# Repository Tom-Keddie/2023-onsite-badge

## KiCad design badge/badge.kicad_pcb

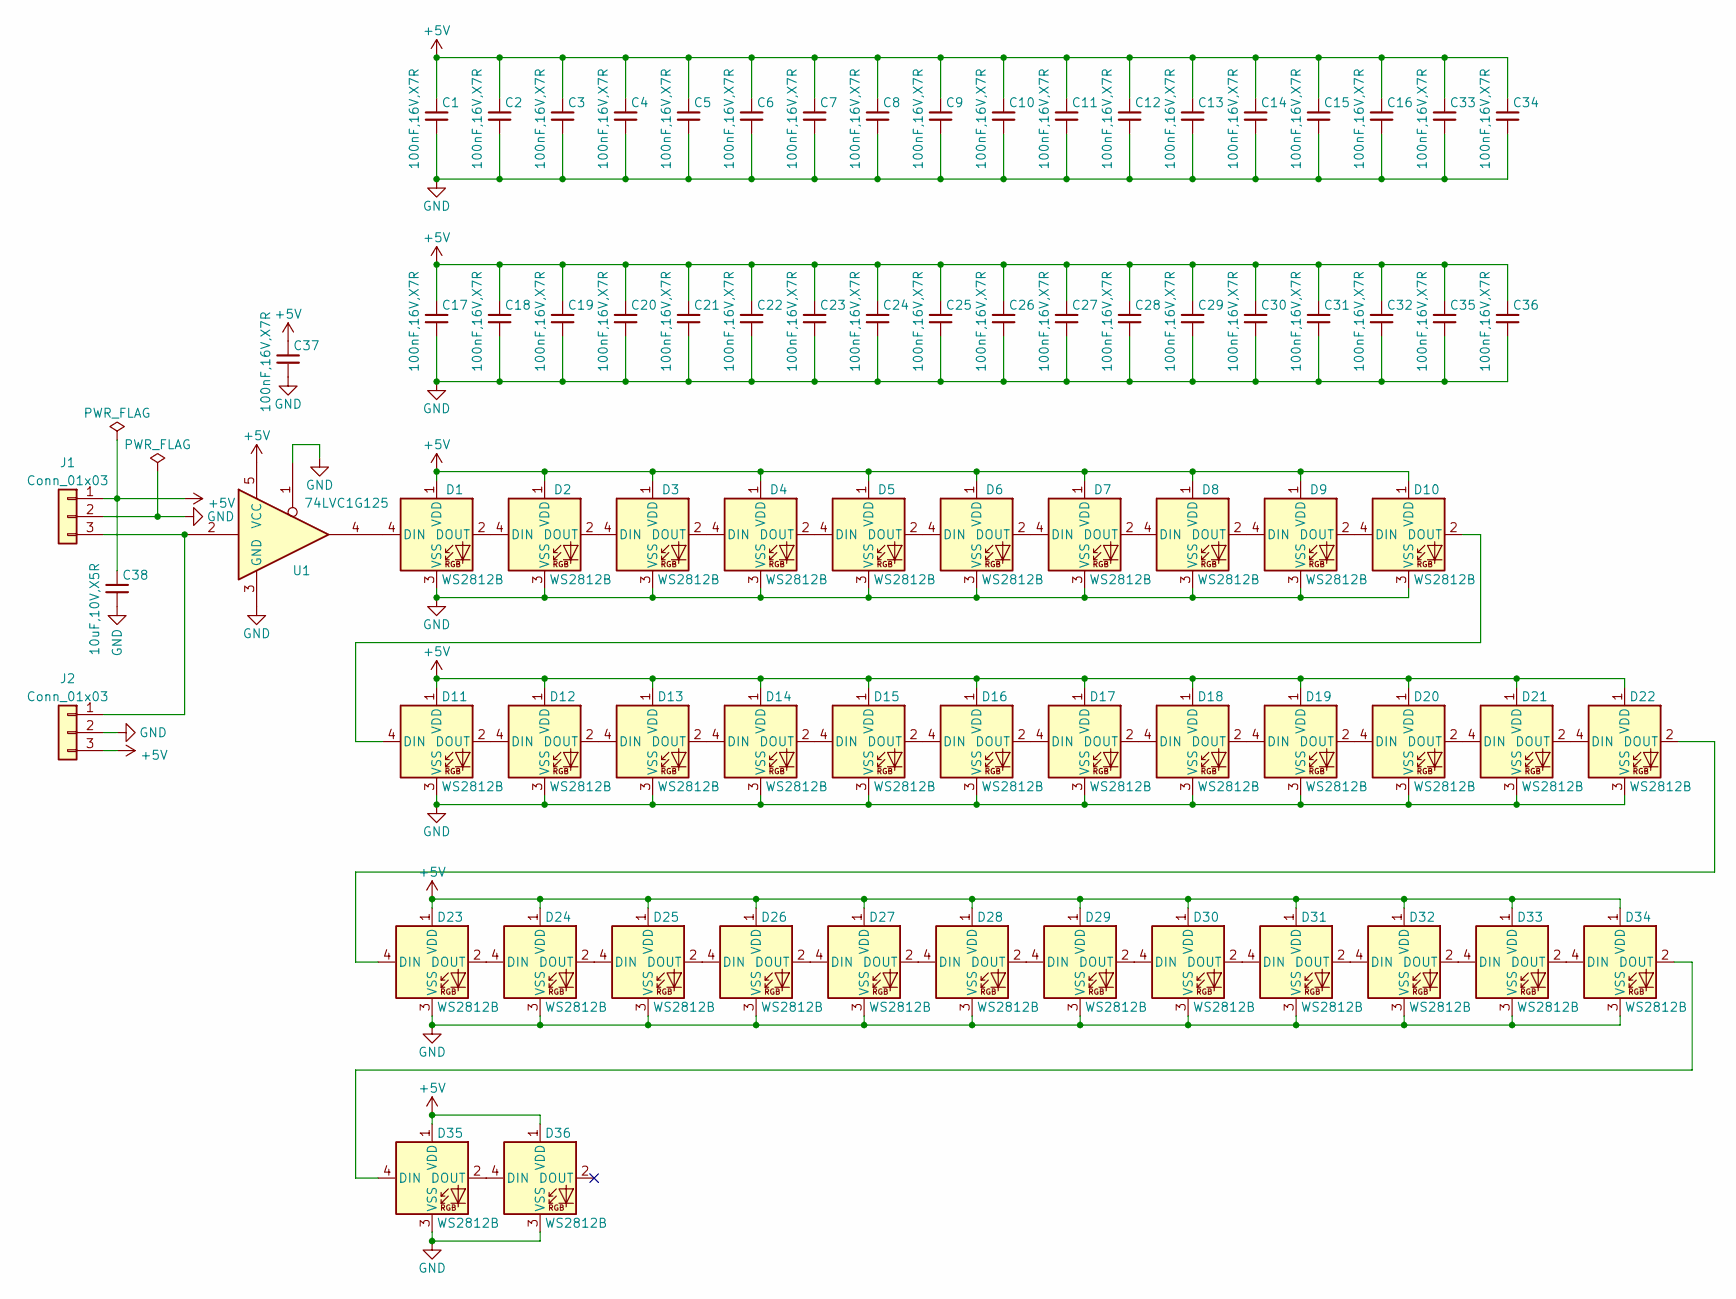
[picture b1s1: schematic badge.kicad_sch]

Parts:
C1, C2, C3, C4, C5, C6, C7, C8, C9, C10, C11, C12, C13, C14, C15, C16, C17, C18, C19, C20, C21, C22, C23, C24, C25, C26, C27, C28, C29, C30, C31, C32, C33, C34, C35, C36, C37: 100nF,16V,X7R; C_0402_1005Metric; MFGPN CL05B104KO5NNNC; LCSC C1525
C38: 10uF,10V,X5R; C_0603_1608Metric; MFGPN CL10A106KP8NNNC; LCSC C19702
D1, D2, D3, D4, D5, D6, D7, D8, D9, D10, D11, D12, D13, D14, D15, D16, D17, D18, D19, D20, D21, D22, D23, D24, D25, D26, D27, D28, D29, D30, D31, D32, D33, D34, D35, D36: WS2812B; LED_WS2812B_PLCC4_5.0x5.0mm_P3.2mm; LCSC C2843785
J1, J2: Conn_01x03; PinHeader_1x03_P2.54mm_Horizontal_SMD
U1: 74LVC1G125; SOT-23-5; LCSC C23654

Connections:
+5V: C1.1, C2.1, C3.1, C4.1, C5.1, C6.1, C7.1, C8.1, C9.1, C10.1, C11.1, C12.1, C13.1, C14.1, C15.1, C16.1, C17.1, C18.1, C19.1, C20.1, C21.1, C22.1, C23.1, C24.1, C25.1, C26.1, C27.1, C28.1, C29.1, C30.1, C31.1, C32.1, C33.1, C34.1, C35.1, C36.1, C37.1, C38.1, D1.1 (VDD), D2.1 (VDD), D3.1 (VDD), D4.1 (VDD), D5.1 (VDD), D6.1 (VDD), D7.1 (VDD), D8.1 (VDD), D9.1 (VDD), D10.1 (VDD), D11.1 (VDD), D12.1 (VDD), D13.1 (VDD), D14.1 (VDD), D15.1 (VDD), D16.1 (VDD), D17.1 (VDD), D18.1 (VDD), D19.1 (VDD), D20.1 (VDD), D21.1 (VDD), D22.1 (VDD), D23.1 (VDD), D24.1 (VDD), D25.1 (VDD), D26.1 (VDD), D27.1 (VDD), D28.1 (VDD), D29.1 (VDD), D30.1 (VDD), D31.1 (VDD), D32.1 (VDD), D33.1 (VDD), D34.1 (VDD), D35.1 (VDD), D36.1 (VDD), J1.1, J2.3, U1.5 (VCC)
GND: C1.2, C2.2, C3.2, C4.2, C5.2, C6.2, C7.2, C8.2, C9.2, C10.2, C11.2, C12.2, C13.2, C14.2, C15.2, C16.2, C17.2, C18.2, C19.2, C20.2, C21.2, C22.2, C23.2, C24.2, C25.2, C26.2, C27.2, C28.2, C29.2, C30.2, C31.2, C32.2, C33.2, C34.2, C35.2, C36.2, C37.2, C38.2, D1.3 (VSS), D2.3 (VSS), D3.3 (VSS), D4.3 (VSS), D5.3 (VSS), D6.3 (VSS), D7.3 (VSS), D8.3 (VSS), D9.3 (VSS), D10.3 (VSS), D11.3 (VSS), D12.3 (VSS), D13.3 (VSS), D14.3 (VSS), D15.3 (VSS), D16.3 (VSS), D17.3 (VSS), D18.3 (VSS), D19.3 (VSS), D20.3 (VSS), D21.3 (VSS), D22.3 (VSS), D23.3 (VSS), D24.3 (VSS), D25.3 (VSS), D26.3 (VSS), D27.3 (VSS), D28.3 (VSS), D29.3 (VSS), D30.3 (VSS), D31.3 (VSS), D32.3 (VSS), D33.3 (VSS), D34.3 (VSS), D35.3 (VSS), D36.3 (VSS), J1.2, J2.2, U1.1, U1.3 (GND)
unnamed: D1.4 (DIN), U1.4
unnamed: D1.2 (DOUT), D2.4 (DIN)
unnamed: D2.2 (DOUT), D3.4 (DIN)
unnamed: D3.2 (DOUT), D4.4 (DIN)
unnamed: D4.2 (DOUT), D5.4 (DIN)
unnamed: D5.2 (DOUT), D6.4 (DIN)
unnamed: D6.2 (DOUT), D7.4 (DIN)
unnamed: D7.2 (DOUT), D8.4 (DIN)
unnamed: D8.2 (DOUT), D9.4 (DIN)
unnamed: D9.2 (DOUT), D10.4 (DIN)
unnamed: D10.2 (DOUT), D11.4 (DIN)
unnamed: D11.2 (DOUT), D12.4 (DIN)
unnamed: D12.2 (DOUT), D13.4 (DIN)
unnamed: D13.2 (DOUT), D14.4 (DIN)
unnamed: D14.2 (DOUT), D15.4 (DIN)
unnamed: D15.2 (DOUT), D16.4 (DIN)
unnamed: D16.2 (DOUT), D17.4 (DIN)
unnamed: D17.2 (DOUT), D18.4 (DIN)
unnamed: D18.2 (DOUT), D19.4 (DIN)
unnamed: D19.2 (DOUT), D20.4 (DIN)
unnamed: D20.2 (DOUT), D21.4 (DIN)
unnamed: D21.2 (DOUT), D22.4 (DIN)
unnamed: D22.2 (DOUT), D23.4 (DIN)
unnamed: D23.2 (DOUT), D24.4 (DIN)
unnamed: D24.2 (DOUT), D25.4 (DIN)
unnamed: D25.2 (DOUT), D26.4 (DIN)
unnamed: D26.2 (DOUT), D27.4 (DIN)
unnamed: D27.2 (DOUT), D28.4 (DIN)
unnamed: D28.2 (DOUT), D29.4 (DIN)
unnamed: D29.2 (DOUT), D30.4 (DIN)
unnamed: D30.2 (DOUT), D31.4 (DIN)
unnamed: D31.2 (DOUT), D32.4 (DIN)
unnamed: D32.2 (DOUT), D33.4 (DIN)
unnamed: D33.2 (DOUT), D34.4 (DIN)
unnamed: D34.2 (DOUT), D35.4 (DIN)
unnamed: D35.2 (DOUT), D36.4 (DIN)
unnamed: J1.3, J2.1, U1.2

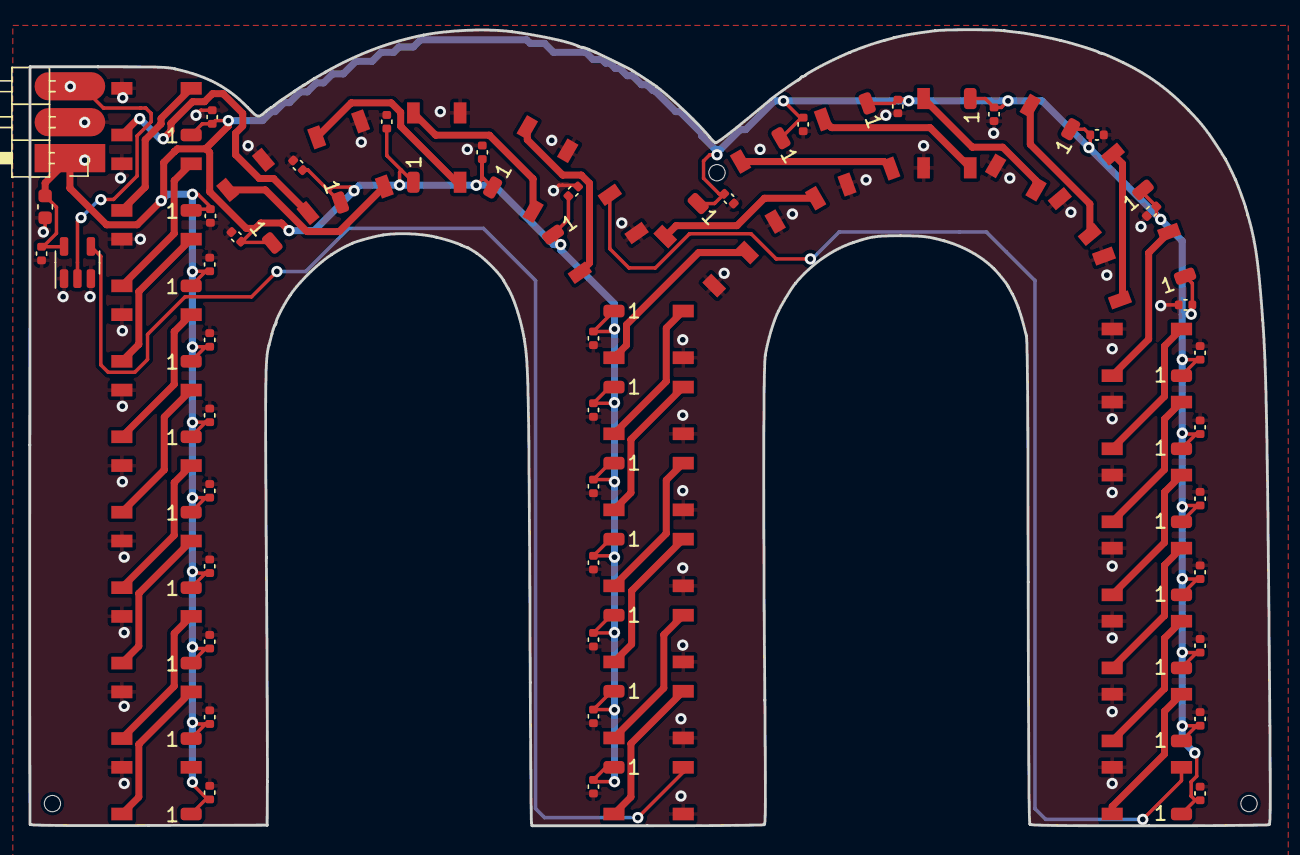
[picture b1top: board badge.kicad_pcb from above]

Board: 2 copper layers, 87.7 x 56.3 mm, 77 parts (1 on the bottom side), 39 nets.

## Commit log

2023-03-04 image: add minim mark png/dxf
2023-03-04 badge: add edge library footprint
2023-03-05 badge: placement mostly complete
2023-03-05 badge: add caps for leds
2023-03-06 badeg: complete
2023-03-23 badge: ver 1.1 ready for production
2023-03-27 badge: added step file generation to Makefile
